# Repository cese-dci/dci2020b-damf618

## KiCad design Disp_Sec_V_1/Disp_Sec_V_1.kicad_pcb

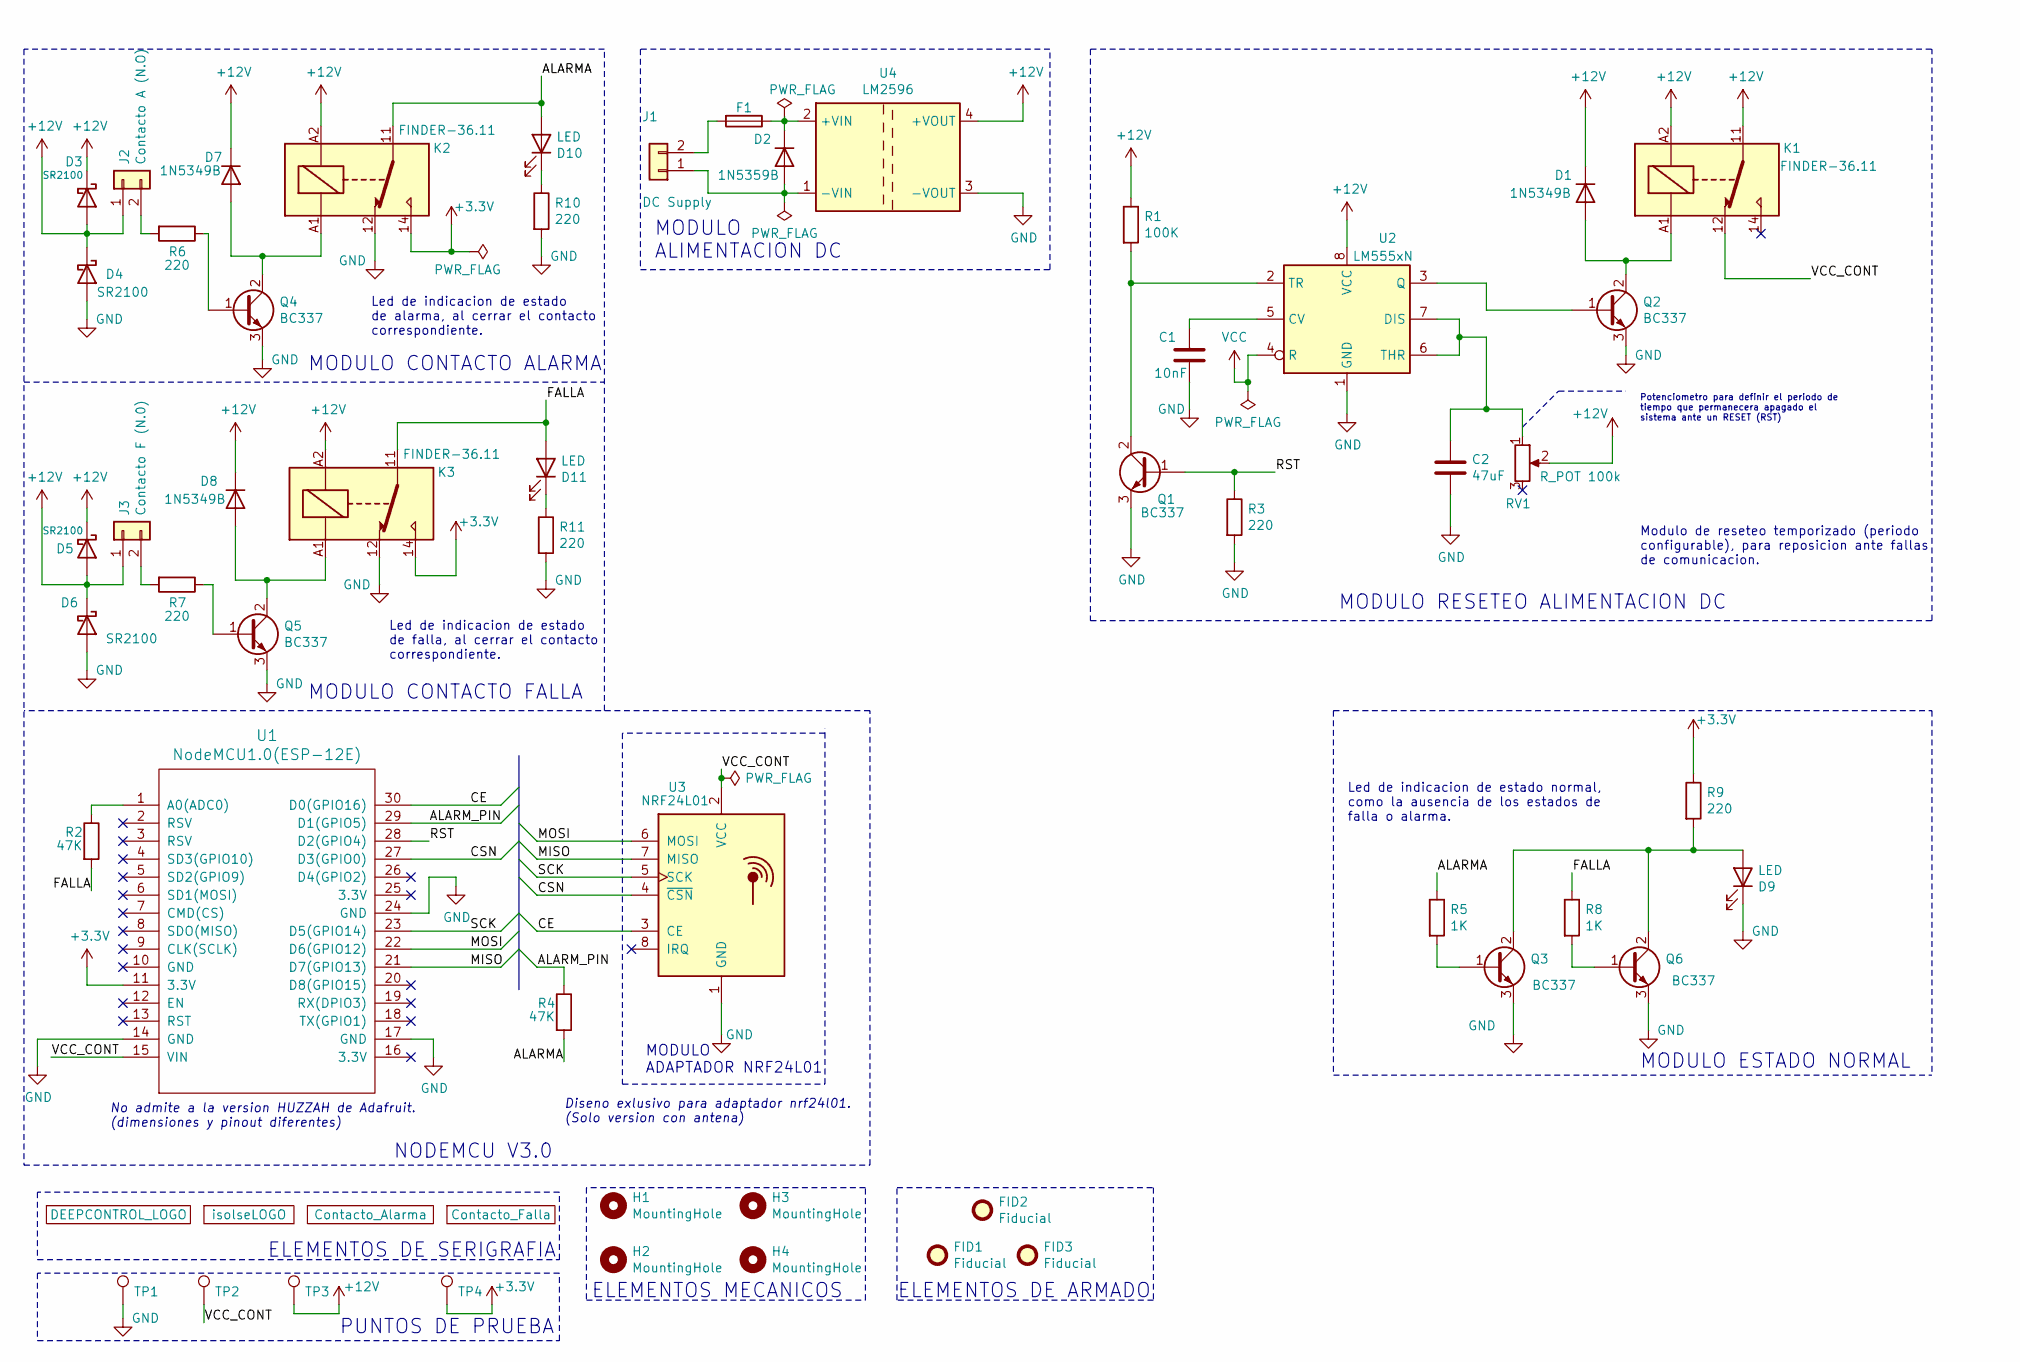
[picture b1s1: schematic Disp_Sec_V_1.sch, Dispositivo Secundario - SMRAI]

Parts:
C1: 10nF; CP_Radial_D4.0mm_P1.50mm
C2: 47uF; CP_Radial_D4.0mm_P1.50mm
D1, D7, D8: 1N5349B; D_A-405_P10.16mm_Horizontal
D2: 1N5359B; D_A-405_P10.16mm_Horizontal
D3, D4, D5, D6: SR2100; D_DO-34_SOD68_P10.16mm_Horizontal
D9, D10, D11: LED; LED_D3.0mm
F1: 100mA (5 x 20); Fuse
FID1, FID2, FID3: Fiducial; Fiducial_1mm_Mask2mm
H1, H2, H3, H4: MountingHole; MountingHole_2.5mm
J1: DC Supply; JST_EH_B2B-EH-A_1x02_P2.50mm_Vertical
J2: Contacto A (N.O); TerminalBlock_Phoenix_MKDS-1,5-2-5.08_1x02_P5.08mm_Horizont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
J3: Contacto F (N.0); TerminalBlock_Phoenix_MKDS-1,5-2-5.08_1x02_P5.08mm_Horizont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
K1, K2, K3: FINDER-36.11; Relay_SPDT_Finder_36.11
Q1, Q2, Q3, Q4, Q5, Q6: BC337; NEC_Molded_7x4x9mm
R1: 100K; R_Axial_DIN0411_L9.9mm_D3.6mm_P12.70mm_Horizontal
R2, R4: 47K; R_Axial_DIN0411_L9.9mm_D3.6mm_P12.70mm_Horizontal
R3, R6, R7, R9, R10, R11: 220; R_Axial_DIN0411_L9.9mm_D3.6mm_P12.70mm_Horizontal
R5, R8: 1K; R_Axial_DIN0411_L9.9mm_D3.6mm_P12.70mm_Horizontal
RV1: R_POT 100k; Potentiometer_Bourns_3266W_Vertical
TP1, TP2, TP3, TP4: TestPoint; TestPoint_Loop_D1.80mm_Drill1.0mm_Beaded
U1: NodeMCU1.0(ESP-12E); NodeMCU1.0
U2: LM555xN; DIP-8_W7.62mm
U3: NRF24L01; nRF24L01_Adapter
U4: LM2596; DC_DC_Converter_lm2596
U5: DEEPCONTROL_LOGO; DC
U6: isolseLOGO; isolse
U7: Contacto_Falla; C.FALLA
U8: Contacto_Alarma; C.ALARMA

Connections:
+3V3: K2.14, K3.14, R9.1, TP4.1, U1.11 (3.3V)
+12V: D1.1 (K), D3.1 (K), D3.2 (A), D4.1 (K), D5.1 (K), D5.2 (A), D6.1 (K), D7.1 (K), D8.1 (K), J2.1, J3.1, K1.11, K1.A2, K2.A2, K3.A2, R1.1, RV1.2, TP3.1, U2.8 (VCC), U4.4 (+VOUT)
/ALARMA: D10.2 (A), K2.11, R4.2, R5.1
/ALARM_PIN: R4.1, U1.29 (D1(GPIO5))
/CE: U1.30 (D0(GPIO16)), U3.3 (CE)
/CSN: U1.27 (D3(GPIO0)), U3.4 (~CSN)
/FALLA: D11.2 (A), K3.11, R2.2, R8.1
/MISO: U1.21 (D7(GPIO13)), U3.7 (MISO)
/MOSI: U1.22 (D6(GPIO12)), U3.6 (MOSI)
/RST: Q1.1 (B), R3.1, U1.28 (D2(GPIO4))
/SCK: U1.23 (D5(GPIO14)), U3.5 (SCK)
/VCC_CONT: K1.12, TP2.1, U1.15 (VIN), U3.2 (VCC)
GND: C1.2, C2.2, D4.2 (A), D6.2 (A), D9.1 (K), K2.12, K3.12, Q1.3 (E), Q2.3 (E), Q3.3 (E), Q4.3 (E), Q5.3 (E), Q6.3 (E), R3.2, R10.2, R11.2, TP1.1, U1.14 (GND), U1.17 (GND), U1.24 (GND), U2.1 (GND), U3.1 (GND), U4.3 (-VOUT)
unnamed: C1.1, U2.5 (CV)
unnamed: C2.1, RV1.1, U2.6 (THR), U2.7 (DIS)
unnamed: D1.2 (A), K1.A1, Q2.2 (C)
unnamed: D2.1 (K), F1.1, U4.2 (+VIN)
unnamed: D2.2 (A), J1.1, U4.1 (-VIN)
unnamed: D7.2 (A), K2.A1, Q4.2 (C)
unnamed: D8.2 (A), K3.A1, Q5.2 (C)
unnamed: D9.2 (A), Q3.2 (C), Q6.2 (C), R9.2
unnamed: D10.1 (K), R10.1
unnamed: D11.1 (K), R11.1
unnamed: F1.2, J1.2
unnamed: J2.2, R6.2
unnamed: J3.2, R7.2
unnamed: Q1.2 (C), R1.2, U2.2 (TR)
unnamed: Q2.1 (B), U2.3 (Q)
unnamed: Q3.1 (B), R5.2
unnamed: Q4.1 (B), R6.1
unnamed: Q5.1 (B), R7.1
unnamed: Q6.1 (B), R8.2
unnamed: R2.1, U1.1 (A0(ADC0))
VCC: U2.4 (R)

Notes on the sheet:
MODULO RESETEO ALIMENTACION DC
MODULO ADAPTADOR NRF24L01
MODULO ALIMENTACION DC
NODEMCU V3.0
Potenciometro para definir el periodo de tiempo que permanecera apagado el sistema ante un RESET (RST)
Diseno exlusivo para adaptador nrf24l01. (Solo version con antena)
No admite a la version HUZZAH de Adafruit. (dimensiones y pinout diferentes)
Modulo de reseteo temporizado (periodo configurable), para reposicion ante fallas de comunicacion.
ELEMENTOS MECANICOS
ELEMENTOS DE SERIGRAFIA
Led de indicacion de estado de alarma, al cerrar el contacto correspondiente.
Led de indicacion de estado de falla, al cerrar el contacto correspondiente.
MODULO CONTACTO ALARMA
MODULO CONTACTO FALLA
MODULO ESTADO NORMAL
Led de indicacion de estado normal, como la ausencia de los estados de falla o alarma.
ELEMENTOS DE ARMADO
PUNTOS DE PRUEBA

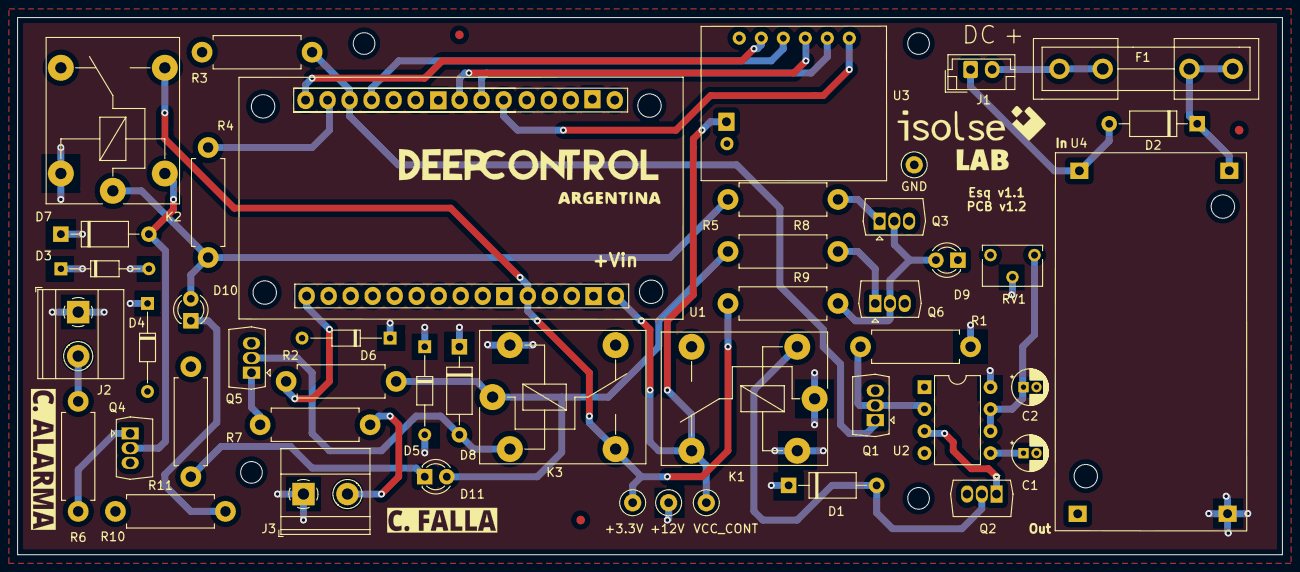
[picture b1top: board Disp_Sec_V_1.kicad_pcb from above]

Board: 2 copper layers, 146.0 x 62.0 mm, 57 parts (0 on the bottom side), 33 nets.

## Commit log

2020-09-26 Avances PCB
2020-09-26 Modificacion de NodeMCU Footprint
2020-10-04 Disminuir Area,GND, VCC y nuevo logo
2020-10-05 Licencia
2020-10-14 Correcciones Finales
2020-10-23 Correcciones de Segunda Revision
2020-10-25 Correcciones de Segunda Revision Fuse 3d
2020-10-27 Correcion: Vias/Soldadura Back
